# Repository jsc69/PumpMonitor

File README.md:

# PumpMonitor

PumpMonitor is a small project to monitor to drainage pumps. There is a main pump and a second pump which kicks in when the main pump do not work.
The pumps are monitored by two LEDs.
1. GREEN: main pump is powered
2. RED: second pump is powered

The ESP32 checks this LEDs and send a WhatsApp message if the second pump runs (red LED is on)

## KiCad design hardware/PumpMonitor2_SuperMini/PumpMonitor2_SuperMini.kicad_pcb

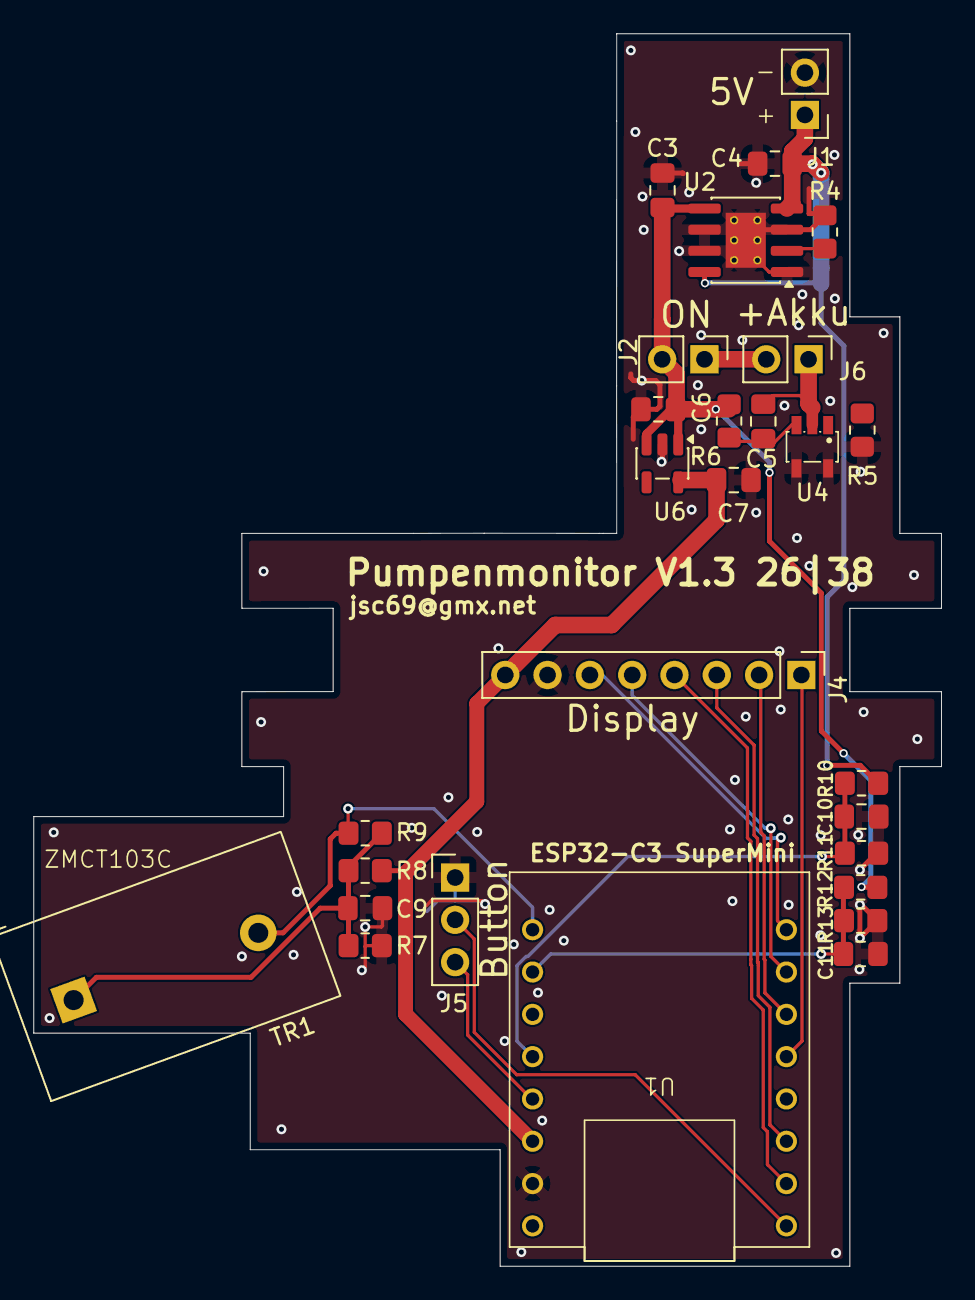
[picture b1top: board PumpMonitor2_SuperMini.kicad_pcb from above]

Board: 2 copper layers, 54.5 x 74.0 mm, 28 parts (0 on the bottom side), 20 nets.

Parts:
C3, C4, C9: 10u; C_0805_2012Metric_Pad1.18x1.45mm_HandSolder
C5, C10, C11: 100n; C_0805_2012Metric_Pad1.18x1.45mm_HandSolder
C6, C7: 2u2; C_0805_2012Metric_Pad1.18x1.45mm_HandSolder
J1, J2, J6: Conn_01x02_Pin; PinHeader_1x02_P2.54mm_Vertical
J4: Conn_01x08_Socket; PinHeader_1x08_P2.54mm_Vertical
J5: Conn_01x03_Pin; PinHeader_1x03_P2.54mm_Vertical
R4: 4k; R_0805_2012Metric_Pad1.20x1.40mm_HandSolder
R5: 1k; R_0805_2012Metric_Pad1.20x1.40mm_HandSolder
R6, R9: 100; R_0805_2012Metric_Pad1.20x1.40mm_HandSolder
R7, R8, R10, R12, R13: 100k; R_0805_2012Metric_Pad1.20x1.40mm_HandSolder
R11: 180k; R_0805_2012Metric_Pad1.20x1.40mm_HandSolder
TR1: ZMCT103C; Transformer_Zeming_ZMCT103C
U1: ESP32-C3 SuperMini
U2: TP4056-42-ESOP8; SOIC-8-1EP_3.9x4.9mm_P1.27mm_EP2.41x3.3mm_ThermalVias
U4: XB5352A
U6: XC6210B332MR; SOT-23-5

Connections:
+3.3V: C7.1, J4.8, R8.2, U1.14 (3V3), U6.5 (VOUT)
+5V: C4.1, J1.1, R10.2, U2.4 (V_{CC}), U2.8 (CE)
+BATT: C3.1, C6.1, J2.2, R6.2, R12.2, U2.5 (BAT), U6.1 (VIN), U6.3 (CE)
/AKKU_CHECK: C11.1, R12.1, R13.2, U1.10 (GPIO1/DC)
/BTN_DOWN: J5.3, U1.13 (GPIO4/MOSI)
/BTN_UP: J5.2, U1.1 (GPIO5/CS)
/DIS_BUSY: J4.1, U1.5 (GPIO9/SCL)
/DIS_CS: J4.4, U1.2 (GPIO6)
/DIS_DC: J4.3, U1.3 (GPIO7)
/DIS_MOSI: J4.6, U1.8 (GPIO21)
/DIS_RST: J4.2, U1.6 (GPIO10)
/DIS_SCK: J4.5, U1.7 (GPIO20)
/POWER_CHECK: C10.1, R10.1, R11.2, U1.12 (GPIO3/MISO)
/PUMP_CHECK: R9.1, TR1.2, U1.9 (GPIO0/RST)
GND: C3.2, C4.2, C6.2, C7.2, C9.2, C10.2, C11.2, J1.2, J4.7, J5.1, R4.2, R5.1, R7.1, R11.1, R13.1, U1.15 (GND), U2.1 (TEMP), U2.3 (GND), U2.6 (~STDBY), U2.7 (~CHRG), U2.9 (EPAD), U4.4 (VM), U4.5 (VM), U6.2 (GND)
unnamed: C9.1, R7.2, R8.1, R9.2, TR1.1
unnamed: J2.1, J6.2
unnamed: C5.2, J6.1, U4.2 (GND)
unnamed: R4.1, U2.2 (PROG)
unnamed: C5.1, R6.1, U4.3 (VDD)

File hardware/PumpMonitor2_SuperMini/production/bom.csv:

Designator,Footprint,Quantity,Value,LCSC Part #
"C10, C11, C5",0805,3,100n,
"C3, C4, C9",0805,3,10u,
"C6, C7",0805,2,2u2,
"J1, J2, J6",PinHeader_1x02_P2.54mm_Vertical,3,Conn_01x02_Pin,
J4,PinHeader_1x08_P2.54mm_Vertical,1,Conn_01x08_Socket,
J5,PinHeader_1x03_P2.54mm_Vertical,1,Conn_01x03_Pin,
"R10, R12, R13, R7, R8",0805,5,100k,
R11,0805,1,180k,
R4,0805,1,4k,
R5,0805,1,1k,
"R6, R9",0805,2,100,
TR1,Transformer_Zeming_ZMCT103C,1,ZMCT103C,
U1,ESP32-C3 SuperMini,1,~,
U2,SOIC-8-1EP_3.9x4.9mm_P1.27mm_EP2.41x3.3mm_ThermalVias,1,TP4056-42-ESOP8,C16581
U4,XB5352A,1,XB5352A,C154943
U6,SOT-23-5,1,XC6210B332MR,C49375238

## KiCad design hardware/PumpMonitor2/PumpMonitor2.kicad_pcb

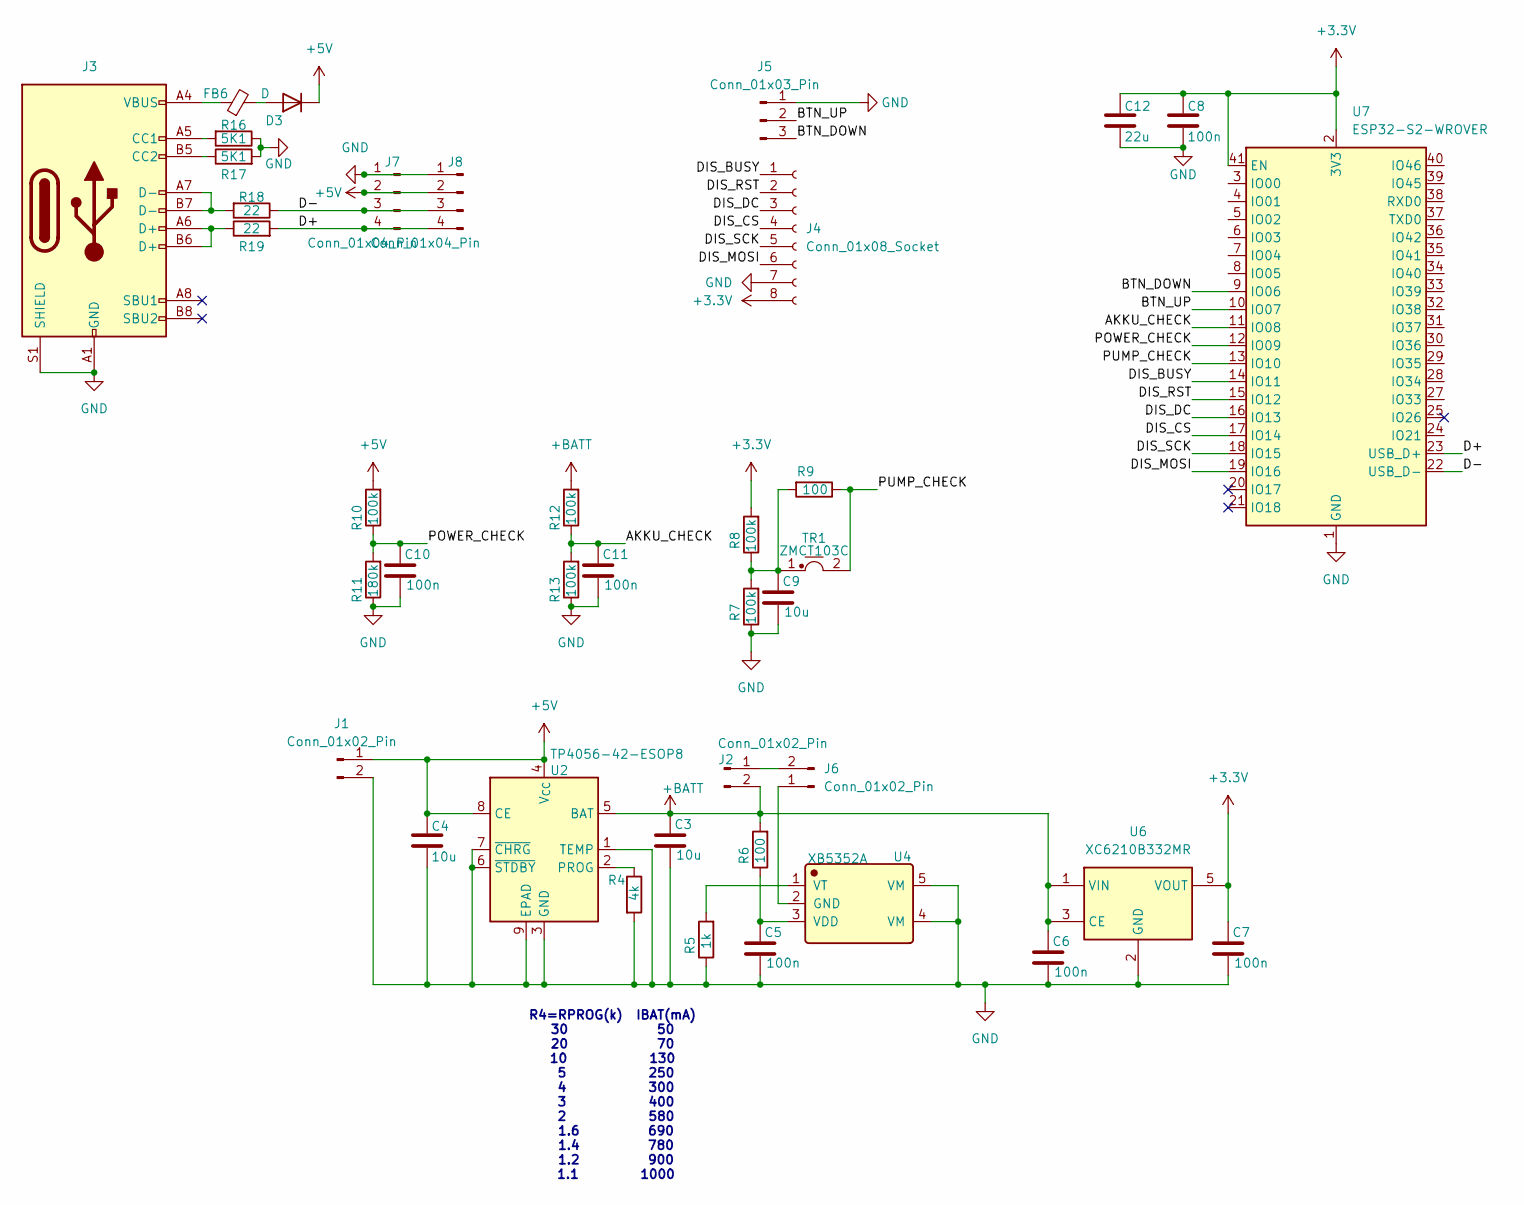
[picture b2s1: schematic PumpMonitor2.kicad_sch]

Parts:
C3, C4, C9: 10u; C_0805_2012Metric_Pad1.18x1.45mm_HandSolder
C5, C6, C7, C8, C10, C11: 100n; C_0805_2012Metric_Pad1.18x1.45mm_HandSolder
C12: 22u; C_0805_2012Metric_Pad1.18x1.45mm_HandSolder
D3: D; Nexperia_CFP3_SOD-123W; LCSC C5120763
FB6: FerriteBead_Small; L_0805_2012Metric; LCSC C963878
J1, J2, J6: Conn_01x02_Pin; PinHeader_1x02_P2.54mm_Vertical
J3: USB_C_Receptacle_USB2.0_16P; LCSC C42400252
J4: Conn_01x08_Socket; PinHeader_1x08_P2.54mm_Vertical
J5: Conn_01x03_Pin; PinHeader_1x03_P2.54mm_Vertical
J7, J8: Conn_01x04_Pin; PinHeader_1x04_P2.54mm_Vertical
R4: 4k; R_0805_2012Metric_Pad1.20x1.40mm_HandSolder
R5: 1k; R_0805_2012Metric_Pad1.20x1.40mm_HandSolder
R6, R9: 100; R_0805_2012Metric_Pad1.20x1.40mm_HandSolder
R7, R8, R10, R12, R13: 100k; R_0805_2012Metric_Pad1.20x1.40mm_HandSolder
R11: 180k; R_0805_2012Metric_Pad1.20x1.40mm_HandSolder
R16, R17: 5K1; R_0805_2012Metric_Pad1.20x1.40mm_HandSolder; LCSC C26000
R18, R19: 22; R_0805_2012Metric_Pad1.20x1.40mm_HandSolder; LCSC C1203
TR1: ZMCT103C; Transformer_Zeming_ZMCT103C
U2: TP4056-42-ESOP8; SOIC-8-1EP_3.9x4.9mm_P1.27mm_EP2.41x3.3mm_ThermalVias; LCSC C16581
U4: XB5352A; Manufacturer Part XB5352A; LCSC C154943
U6: XC6210B332MR; SOT-23-5; LCSC C49375238
U7: ESP32-S2-WROVER

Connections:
+3.3V: C7.1, C8.1, C12.1, J4.8, R8.2, U6.5 (VOUT), U7.2 (3V3), U7.41 (EN)
+5V: C4.1, D3.1 (K), J1.1, J7.2, J8.2, R10.2, U2.4 (V_{CC}), U2.8 (CE)
+BATT: C3.1, C6.1, J2.2, R6.2, R12.2, U2.5 (BAT), U6.1 (VIN), U6.3 (CE)
/AKKU_CHECK: C11.1, R12.1, R13.2, U7.11 (IO08)
/BTN_DOWN: J5.3, U7.9 (IO06)
/BTN_UP: J5.2, U7.10 (IO07)
/D+: J7.4, J8.4, R19.2, U7.23 (USB_D+)
/D-: J7.3, J8.3, R18.1, U7.22 (USB_D-)
/DIS_BUSY: J4.1, U7.14 (IO11)
/DIS_CS: J4.4, U7.17 (IO14)
/DIS_DC: J4.3, U7.16 (IO13)
/DIS_MOSI: J4.6, U7.19 (IO16)
/DIS_RST: J4.2, U7.15 (IO12)
/DIS_SCK: J4.5, U7.18 (IO15)
/POWER_CHECK: C10.1, R10.1, R11.2, U7.12 (IO09)
/PUMP_CHECK: R9.1, TR1.2, U7.13 (IO10)
GND: C3.2, C4.2, C5.2, C6.2, C7.2, C8.2, C9.2, C10.2, C11.2, C12.2, J1.2, J3.A1 (GND), J3.A12 (GND), J3.B1 (GND), J3.B12 (GND), J3.S1 (SHIELD), J4.7, J5.1, J7.1, J8.1, R4.2, R5.1, R7.1, R11.1, R13.1, R16.1, R17.2, U2.1 (TEMP), U2.3 (GND), U2.6 (~STDBY), U2.7 (~CHRG), U2.9 (EPAD), U4.4 (VM), U4.5 (VM), U6.2 (GND), U7.1 (GND), U7.26 (GND), U7.42 (GND), U7.43 (GND)
unnamed: C9.1, R7.2, R8.1, R9.2, TR1.1
unnamed: D3.2 (A), FB6.2
unnamed: FB6.1, J3.A4 (VBUS), J3.A9 (VBUS), J3.B4 (VBUS), J3.B9 (VBUS)
unnamed: J2.1, J6.2
unnamed: J3.A5 (CC1), R16.2
unnamed: J3.B5 (CC2), R17.1
unnamed: J3.A6 (D+), J3.B6 (D+), R19.1
unnamed: J3.A7 (D-), J3.B7 (D-), R18.2
unnamed: J6.1, U4.2 (GND)
unnamed: R4.1, U2.2 (PROG)
unnamed: C5.1, R6.1, U4.3 (VDD)
unnamed: R5.2, U4.1 (VT)

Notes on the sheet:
R4=RPROG(k) IBAT(mA) 30 50 20 70 10 130 5 250 4 300 3 400 2 580 1.6 690 1.4 780 1.2 900 1.1 1000

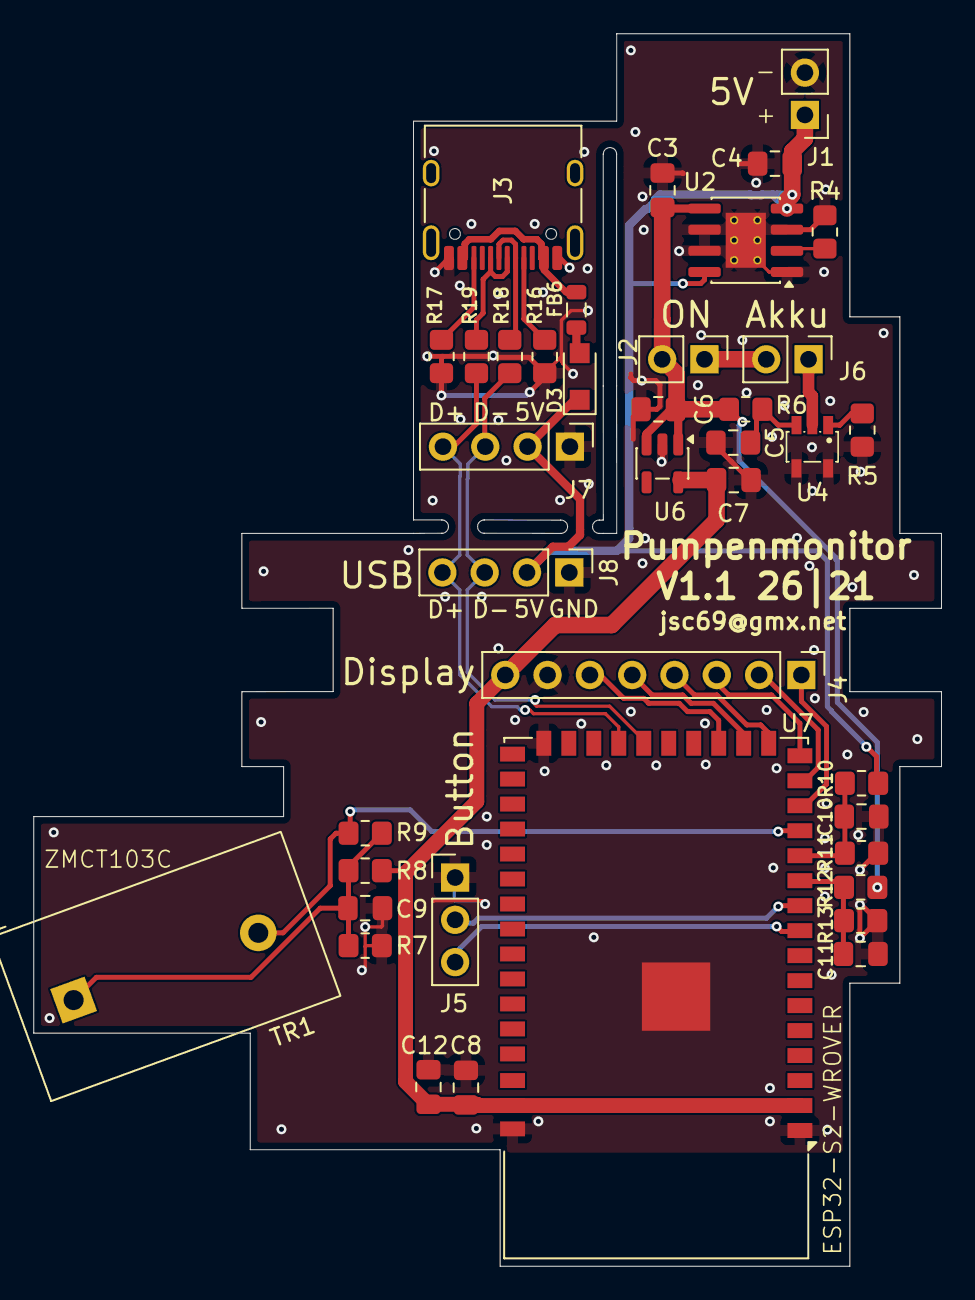
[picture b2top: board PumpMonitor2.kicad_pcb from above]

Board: 2 copper layers, 54.5 x 74.0 mm, 39 parts (0 on the bottom side), 29 nets.

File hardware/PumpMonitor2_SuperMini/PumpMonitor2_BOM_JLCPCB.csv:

Comment,Designator,Footprint,LCSC Part Number
100,"R6,R9",R_0805_2012Metric_Pad1.20x1.40mm_HandSolder,
100k,"R10,R12,R13,R7,R8",R_0805_2012Metric_Pad1.20x1.40mm_HandSolder,
100n,"C10,C11,C5,C6,C7,C8",C_0805_2012Metric_Pad1.18x1.45mm_HandSolder,
10u,"C3,C4,C9",C_0805_2012Metric_Pad1.18x1.45mm_HandSolder,
180k,R11,R_0805_2012Metric_Pad1.20x1.40mm_HandSolder,
1k,R5,R_0805_2012Metric_Pad1.20x1.40mm_HandSolder,
22,"R18,R19",R_0805_2012Metric_Pad1.20x1.40mm_HandSolder,C1203
22u,C12,C_0805_2012Metric_Pad1.18x1.45mm_HandSolder,
4k,R4,R_0805_2012Metric_Pad1.20x1.40mm_HandSolder,
5K1,"R16,R17",R_0805_2012Metric_Pad1.20x1.40mm_HandSolder,C26000
Conn_01x02_Pin,"J1,J2,J6",PinHeader_1x02_P2.54mm_Vertical,
Conn_01x03_Pin,J5,PinHeader_1x03_P2.54mm_Vertical,
Conn_01x04_Pin,"J7,J8",PinHeader_1x04_P2.54mm_Vertical,
Conn_01x08_Socket,J4,PinHeader_1x08_P2.54mm_Vertical,
D,D3,Nexperia_CFP3_SOD-123W,C5120763
ESP32-S2-WROVER,U7,ESP32-S2-WROVER,
FerriteBead_Small,FB6,L_0805_2012Metric,C963878
TP4056-42-ESOP8,U2,SOIC-8-1EP_3.9x4.9mm_P1.27mm_EP2.41x3.3mm_ThermalVias,C16581
USB_C_Receptacle_USB2.0_16P,J3,USB_C_Receptacle_HRO_TYPE-C-31-M-12,C42400252
XB5352A,U4,XB5352A,C154943
XC6210B332MR,U6,SOT-23-5,C49375238
ZMCT103C,TR1,Transformer_Zeming_ZMCT103C,

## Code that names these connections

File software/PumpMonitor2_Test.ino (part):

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#endif

// ── Pin-Definitionen ─────────────────────────────────────────────────────────
#define PIN_DIS_MOSI   2
#define PIN_DIS_SCK    3
#define PIN_DIS_CS     4
#define PIN_DIS_DC     5
#define PIN_DIS_RST    6
#define PIN_DIS_BUSY   7

#define PIN_PUMP_CHECK   8   // ADC1_CH7
#define PIN_POWER_CHECK  9   // ADC1_CH8
#define PIN_AKKU_CHECK  10   // ADC1_CH9

#define PIN_BTN_UP      11
#define PIN_BTN_DOWN    12

// ── Messkonstanten ────────────────────────────────────────────────────────────
// Spannungsteiler AKKU_CHECK: R12=100k (oben), R13=100k (unten)
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  // Offset-Mittelwert messen (DC-Anteil, sollte bei ~Vcc/2 liegen wenn Bias-Netzwerk vorhanden)
  long baseSum = 0;
  for (int i = 0; i < 128; i++) {
    baseSum += analogRead(PIN_PUMP_CHECK);
    delayMicroseconds(50);
  }
  baseline = baseSum / 128;

  // RMS über PUMP_SAMPLES Messungen
  for (int i = 0; i < PUMP_SAMPLES; i++) {
    int raw = analogRead(PIN_PUMP_CHECK) - baseline;
    sumSq += (long)raw * raw;
    delayMicroseconds(20);  // ~50 kHz Abtastrate
  }
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  // Gibt true zurück wenn BTN_UP gedrückt, false bei Timeout oder BTN_DOWN
  unsigned long start = millis();
  while (millis() - start < timeoutMs) {
    if (digitalRead(PIN_BTN_UP) == LOW) {
      delay(50);  // Entprellen
      while (digitalRead(PIN_BTN_UP) == LOW);
      return true;
    }
    if (digitalRead(PIN_BTN_DOWN) == LOW) {
      delay(50);
      while (digitalRead(PIN_BTN_DOWN) == LOW);
      return false;
    }
    delay(10);
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
  Serial.println(F("Drücke BTN_UP (IO11)..."));
  while (!upOk && millis() - start < 8000) {
    if (digitalRead(PIN_BTN_UP) == LOW) {
      upOk = true;
      Serial.println(F("  -> BTN_UP erkannt ✓"));
      delay(300);
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  Serial.println(F("Drücke BTN_DOWN (IO12)..."));
  start = millis();
  while (!downOk && millis() - start < 8000) {
    if (digitalRead(PIN_BTN_DOWN) == LOW) {
      downOk = true;
      Serial.println(F("  -> BTN_DOWN erkannt ✓"));
      delay(300);
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  Serial.println(F("TEST 2: Versorgungsspannungen (ADC)"));
  printSeparator();

  float vBatt  = readVoltageAvg(PIN_AKKU_CHECK)  * AKKU_DIVIDER;
  float v5V    = readVoltageAvg(PIN_POWER_CHECK) * POWER_DIVIDER;

  Serial.print(F("  BATT+   : "));
  Serial.print(vBatt, 2);
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  Serial.println(F("  ADC-Rohwerte (16 Samples):"));
  Serial.print(F("  "));
  for (int i = 0; i < 16; i++) {
    Serial.print(analogRead(PIN_PUMP_CHECK));
    Serial.print(i < 15 ? F(", ") : F("\n"));
    delay(1);
  }
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#ifdef TEST_DISPLAY
  Serial.println(F("  Initialisiere Display..."));

  SPI.begin(PIN_DIS_SCK, -1, PIN_DIS_MOSI, PIN_DIS_CS);
  display.init(115200, true, 2, false);

  Serial.println(F("  Zeige Testbild..."));
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  display.setFullWindow();
  display.firstPage();
  // Messwerte einmalig vor der Darstellung lesen
  float vBattDisp  = readVoltageAvg(PIN_AKKU_CHECK)  * AKKU_DIVIDER;
  float v5VDisp    = readVoltageAvg(PIN_POWER_CHECK) * POWER_DIVIDER;
  float iPumpDisp  = readPumpCurrentRMS() * 1000.0f;  // in mA

  do {
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  analogSetAttenuation(ADC_11db);  // Messbereich 0 – 3.3 V

  // Taster: Active-Low mit internem Pull-Up (kein externer Pull-Up im Schaltplan)
  pinMode(PIN_BTN_UP,   INPUT_PULLUP);
  pinMode(PIN_BTN_DOWN, INPUT_PULLUP);
}

void loop() {
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
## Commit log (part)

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2024-10-29 add gitignore
2024-12-01 init
2024-12-22 add 3D model for box
2025-05-24 add template for credentials.h
2025-05-24 clean ups
2025-05-24 add label.odt
2026-02-22 Wartung
2026-03-21 add version 2
2026-04-04 add test programs and 3d files
2026-04-06 create 2. pcb
2026-05-25 add docu for ESP32-C3
